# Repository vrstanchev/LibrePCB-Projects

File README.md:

# ⚡ LibrePCB-Projects – Open-Source PCB Designs  

🔥 **High-Performance, Open-Source PCB Designs for the Future**  

💻 _No bloated CAD tools—just **LibrePCB**, open-source precision, and efficient circuit design._  

---

## 🛠️ What’s Inside?  

✅ **High-Performance PCB Designs** – Optimized, efficient, and ready for production.  
✅ **Minimalist & Functional** – No unnecessary complexity, just clean, modular layouts.  
✅ **LibrePCB-Optimized** – 100% designed in **LibrePCB**, fully open-source & hackable.  
✅ **Open-Source Hardware (OSHW)** – Because innovation should be **accessible to all**.  

🚀 **This repo is all about pushing hardware forward, the open-source way.**  

---

## 🏗️ Featured Projects  

🚀 **[AVRPICBoard](https://github.com/vrstanchev/LibrePCB-Projects/tree/master/AVRPICBoard)** – AVR & PIC development board for embedded systems.  
⚡ **[PICPICBoard](https://github.com/vrstanchev/LibrePCB-Projects/tree/master/PICPICBoard)** – High-performance PIC microcontroller board.  

_(More projects dropping soon! Stay tuned.)_  

---

## 🔥 Why LibrePCB?  

⚡ **Lightweight & Efficient** – No proprietary lock-in, just streamlined circuit design.  
🔬 **Fully Open-Source** – Community-driven, transparent, and extensible.  
💾 **Optimized for Low-Level & Embedded Systems** – Because hardware should be as efficient as the code running on it.  

📢 **No Eagle. No KiCad. Just pure LibrePCB goodness.**  

---

## 🌍 Where to Find Me  

🌐 **Website** – [vrstanchev.dev](https://vrstanchev.dev)  
🐦 **Twitter/X** – [@vrstanchev](https://twitter.com/vrstanchev)  
🎥 **YouTube & Twitch** – [Live Coding & Hardware Hacking](https://www.twitch.tv/vrstanchev)  
📧 **Contact** – hello@vrstanchev.dev  

💰 **Want to support my work?** Stay tuned for sponsorship options!  

---

## 🚀 Join the Movement  

🔥 _Hardware should be open, efficient, and powerful. Let’s build it together._ 🚀  

👊 **Follow, fork, and contribute to LibrePCB-Projects!**

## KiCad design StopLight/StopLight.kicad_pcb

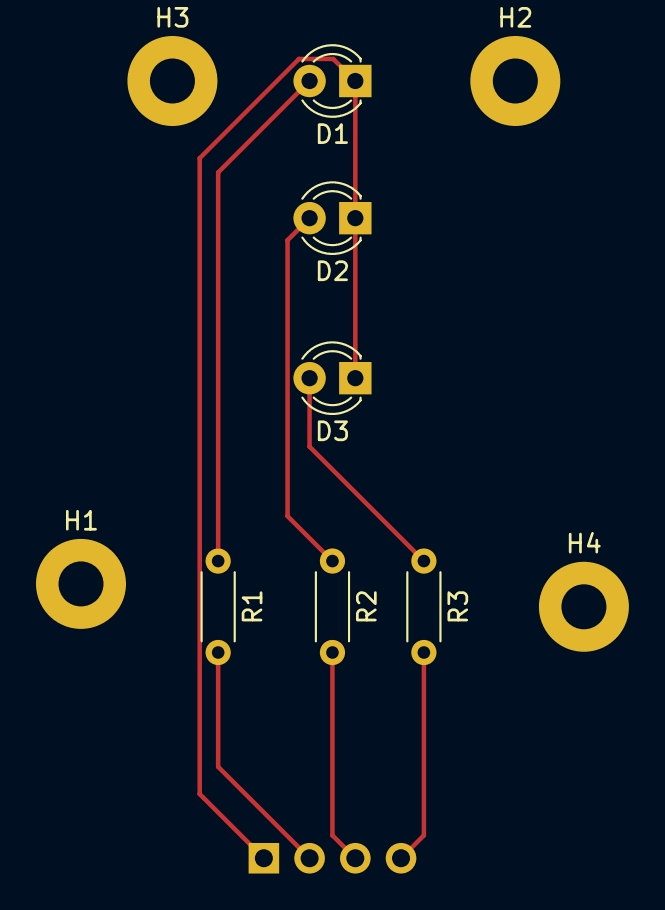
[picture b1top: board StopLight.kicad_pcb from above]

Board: 2 copper layers, 11 parts (1 on the bottom side), 7 nets.

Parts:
D1, D2, D3: LED; LED_D3.0mm
H1, H2, H3, H4: MountingHole; MountingHole_2.5mm_Pad
J1: Conn_01x04; PinHeader_1x04_P2.54mm_Horizontal
R1, R2, R3: R; R_Axial_DIN0204_L3.6mm_D1.6mm_P5.08mm_Horizontal

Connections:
unnamed: D1.1, D2.1, D3.1, J1.1
unnamed: D1.2, R1.1
unnamed: D2.2, R2.1
unnamed: D3.2, R3.1
unnamed: J1.2, R1.2
unnamed: J1.3, R2.2
unnamed: J1.4, R3.2

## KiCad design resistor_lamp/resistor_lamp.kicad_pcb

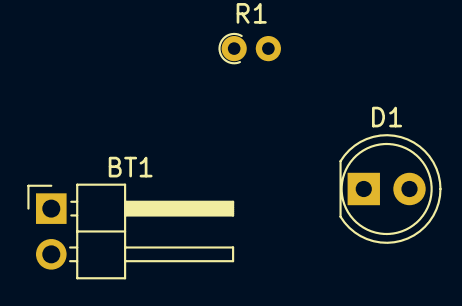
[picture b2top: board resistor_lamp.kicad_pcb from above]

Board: 2 copper layers, 3 parts (0 on the bottom side), 3 nets.

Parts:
BT1: 9V; PinHeader_1x02_P2.54mm_Horizontal
D1: 2V RED; LED_D5.0mm
R1: 470; R_Axial_DIN0204_L3.6mm_D1.6mm_P1.90mm_Vertical

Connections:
unnamed: BT1.1, R1.1
unnamed: BT1.2, D1.1
unnamed: D1.2, R1.2

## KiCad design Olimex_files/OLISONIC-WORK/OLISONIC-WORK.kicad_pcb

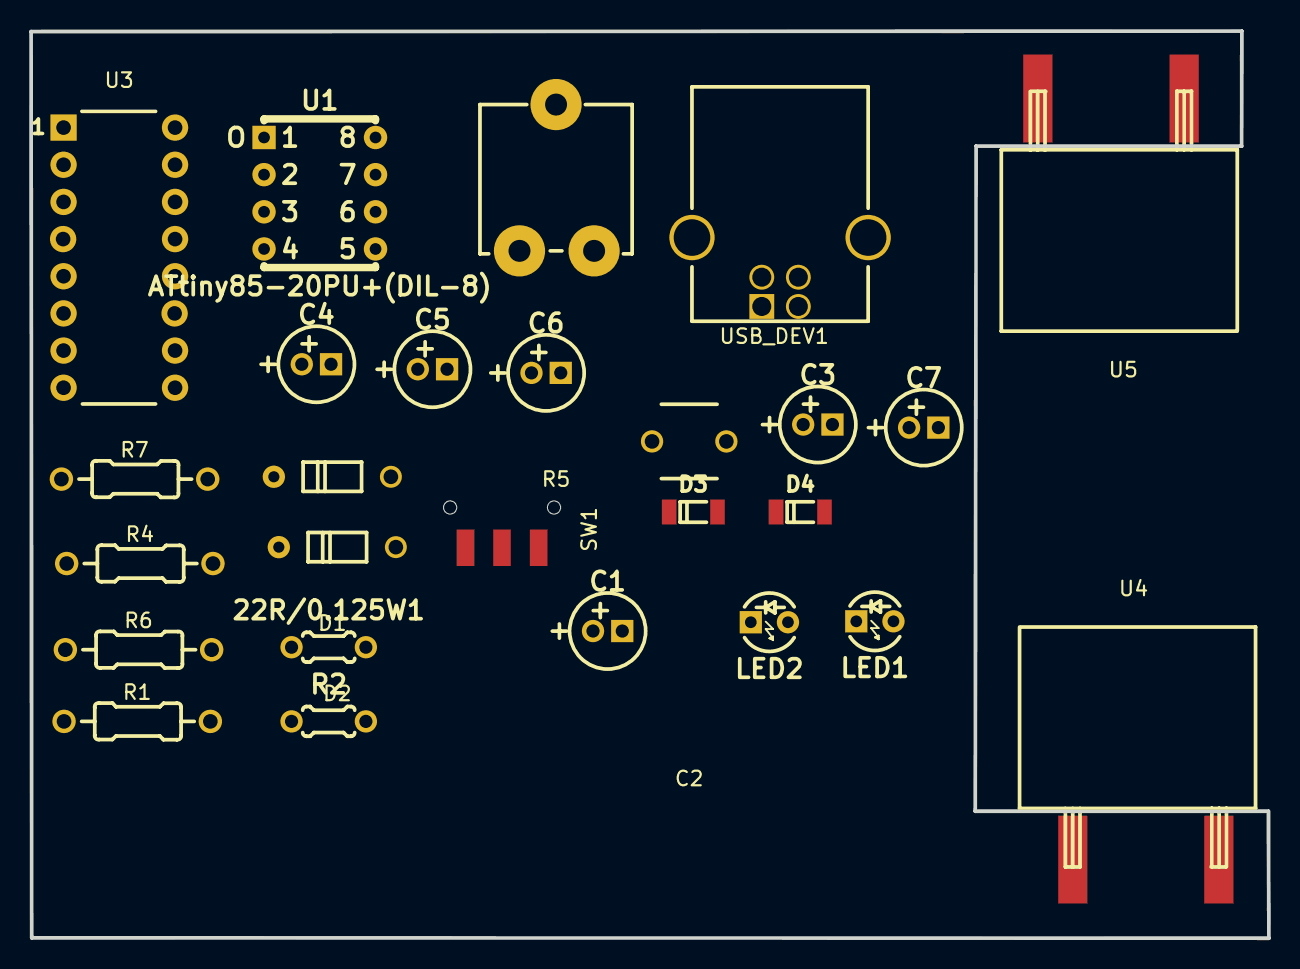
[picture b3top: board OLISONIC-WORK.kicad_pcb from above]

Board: 2 copper layers, 84.6 x 62.0 mm, 26 parts (0 on the bottom side), 22 nets, no tracks yet.

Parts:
22R/0.125W1: R5; R_0.125W_PTH
C1: 10uF/16V/105C; CPOL-RM2mm_5x11mm_PTH
C2: 100nF/2010; 1uF_capacitor_fpt
C3, C4, C5, C6, C7: 4.7uF/50V; CPOL-RM2mm_5x11mm_PTH
D1, D2: 1N4148/DO35; diode
D3, D4: NA(BZV55C3V6/SOD80C); SOD80C-4148-KA
LED1: PWR LED/3mm/Green; LED-3mm-PTH-KA
LED2: LED/3mm/Red; LED-3mm-PTH-KA
R1, R7: 1.5k/0.25W; R_0.25W_PTH
R2: 1.5k/0.25W; R_0.125W_PTH
R4: 22R/0.125W; R_0.25W_PTH
R5: Potentiometer; potentiometer_fpr
R6: NA; R_0.25W_PTH
SW1: TSR-1(T1101GP/6x3x4.3); IT1280A
U1: ATtiny85-20PU+(DIL-8); PDIP-8
U3: MAX232EN; MAX232
U4, U5: Buzzer_2015; ULTRASONIC_HORISONTAL
USB_DEV1: USB-B

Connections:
+5V: C6.2, C7.2, D2.2, U3.16, USB_DEV1.1
GND: C1.2, C2.2, C3.1, C7.1, D3.2, D4.2, LED1.1, LED2.1, R5.3, SW1.1, U1.4, U3.8, U3.15, USB_DEV1.0, USB_DEV1.4
unnamed: 22R/0.125W1.1, D3.1, USB_DEV1.3
unnamed: 22R/0.125W1.2, U1.3
unnamed: C1.1, C2.1, D1.1, R1.1, R2.1, R6.1, U1.8
unnamed: C3.2, U3.6
unnamed: C4.1, U3.1
unnamed: C4.2, U3.3
unnamed: C5.1, U3.4
unnamed: C5.2, U3.5
unnamed: C6.1, U3.2
unnamed: D1.2, D2.1
unnamed: D4.1, R2.2, R4.1, USB_DEV1.2
unnamed: LED1.2, R1.2
unnamed: LED2.2, R7.2
unnamed: R4.2, U1.2
unnamed: R5.2, U1.7
unnamed: R6.2, SW1.2, U1.1
PB0_OC0A: U1.5, U3.11
PB1_OCOB: R7.1, U1.6, U3.10
spout1: U3.14, U4.1, U5.1
spout2: U3.7, U4.2, U5.2

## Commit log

2020-02-19 Simple lamp electrical circuit
2020-02-19 SImple Not Gate electrical circuit
2020-02-19 Kicad first project
2020-12-23 resistor plus Led lamp electrical circuit Schematic and pcb
2022-04-24 StopLight board for Arduino
2022-05-01 Attiny85 circuit schemathic
2022-07-19 test
2022-07-20 livitation
2022-07-23 Kicad Master Degree Project
2022-08-13 avr proj started
2022-08-13 Component Library
2022-08-15 OLISONIC-WORK
2022-08-15 OLISONIC-WORK first work project
2022-08-15 moved
2022-09-10 Master Degree Project
2023-03-16 removed junk
2023-06-13 atmega library added
2023-06-13 Atmegalib zip
2023-06-13 tmp_5chasa
2023-06-14 project added
2023-06-14 Library updated
2023-06-20 uploaded ATtiny85-I2C
2023-06-20 updated library
2023-06-22 update uploaded
2023-06-23 Create LICENSE
2023-06-26 routed board
2023-07-06 updated routed
2023-07-19 Documentation Added
2023-08-03 board Certificated OSHWA
2023-08-03 OSHWA badge added
2023-08-03 CC-BY-SA-4.0 readme added
2023-08-12 Atmega.lplib.zip
    Atmega.lplib.zip upl
2023-08-14 Schematic-values fixed
2023-08-14 CC-BY-SA 4.0 License Updated
2023-08-14 GPLv3 License Updated
2023-08-15 Repo README Updated
2023-08-15 PICPIC name updated
2023-08-16 атт-85
2023-08-18 projects updated
2023-08-20 fixed paper
2023-08-21 Rename CC BY-SA 4.0 to license
2023-08-30 README uploaded
2023-09-24 updated 3Ds
2023-09-26 software added
2023-09-26 Makefile uploaded
2023-09-26 software finished
2023-11-06 Update README.md
    wokwi update
2023-11-14 ATT85 Updated
2023-11-14 uploaded
2023-11-15 AVRPIC Board v1
2023-11-15 AVRPIC Board v1 3D img added
2023-11-15 Rename README.md to README-v1.0.md
2023-11-15 Rename README-v1.0.md to README.md
2023-12-11 released-done
2024-01-05 gplv3 png added
2024-01-05 cc-by-sa png added
